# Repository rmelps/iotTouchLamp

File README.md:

<h1> Touch Lamp </h1>
<ul> 
<li> RGB LED lamp with color control through capacitive touch. </li>
<li> Wifi synchronization through each lamp in a system </li>
<li> ATMega168 Microcontroller project </li>
<li><i>Schematic coming soon</i></li>
</ul>

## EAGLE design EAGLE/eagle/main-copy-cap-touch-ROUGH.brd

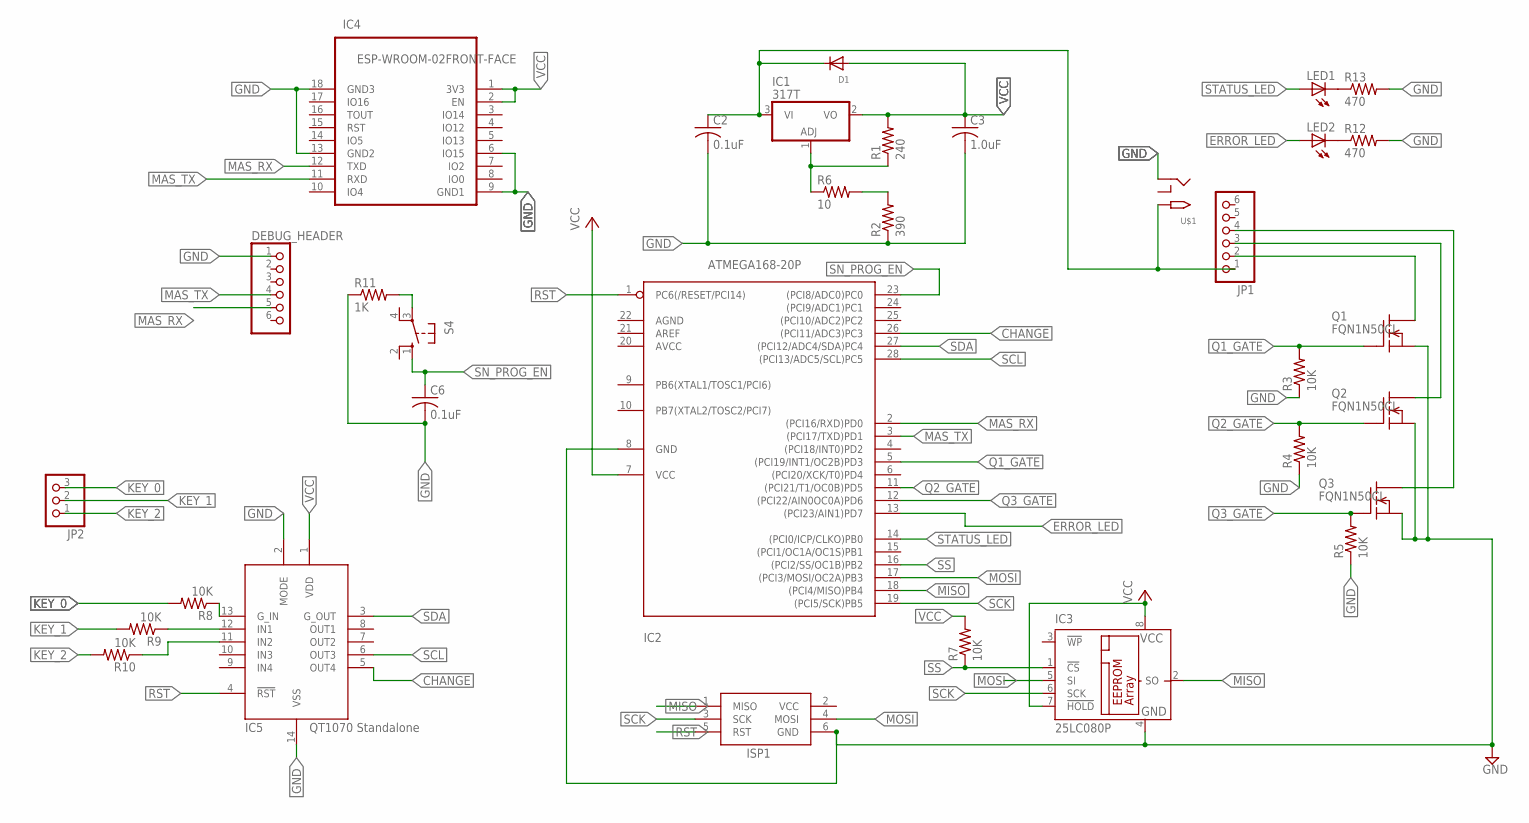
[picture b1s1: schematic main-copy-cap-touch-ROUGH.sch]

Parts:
C2, C6: 0.1uF; C025-030X050
C3: 1.0uF; C025-030X050
D1: DIODEDO-1N4148; DO-1N4148
DEBUG_HEADER: PINHD-1X6B; 1X06-BIG
IC1: 317T; TO220H
IC2: ATMEGA168-20P; DIL28-3
IC3: 25LC080P; DIL8
IC4: ESP-WROOM-02FRONT-FACE; FRONT-FACE
IC5: AT42QT1070-SSU; SO14
ISP1: AVRISP-6; AVRISP
JP1: PINHD-1X6B; 1X06-BIG
JP2: PINHD-1X3; 1X03
LED1, LED2: LED5MM
Q1, Q2, Q3: FQN1N50CI; TO92-INLINE
R1: 240; 0204/7
R2: 390; 0204/7
R3, R4, R5, R7, R8, R9, R10: 10K; 0204/7
R6: 10; 0204/7
R11: 1K; 0204/7
R12, R13: 470; 0204/7
S4: 10-XX; B3F-10XX
U$1: 2.1MMJACKTHM; PJ-102A

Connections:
CHANGE: IC2.26 ((PCI11/ADC3)PC3), IC5.5 (OUT4)
ERROR_LED: IC2.13 ((PCI23/AIN1)PD7), LED2.A
GND: C2.2, C3.2, C6.2, DEBUG_HEADER.1, IC2.8 (GND), IC3.4 (GND), IC4.6 (IO15), IC4.9 (GND1), IC4.13 (GND2), IC4.18 (GND3), IC5.2 (MODE), IC5.14 (VSS), ISP1.6 (GND), Q1.3 (S), Q2.3 (S), Q3.3 (S), R2.1, R3.1, R4.1, R5.1, R11.1, R12.2, R13.2, U$1.RING
KEY_0: JP2.3, R8.2
KEY_1: JP2.2, R9.2
KEY_2: JP2.1, R10.2
MAS_RX: DEBUG_HEADER.5, IC2.2 ((PCI16/RXD)PD0), IC4.12 (TXD)
MAS_TX: DEBUG_HEADER.4, IC2.3 ((PCI17/TXD)PD1), IC4.11 (RXD)
MISO: IC2.18 ((PCI4/MISO)PB4), IC3.2 (SO), ISP1.1 (MISO)
MOSI: IC2.17 ((PCI3/MOSI/OC2A)PB3), IC3.5 (SI), ISP1.4 (MOSI)
unnamed: IC5.13 (G_IN), R8.1
unnamed: IC5.12 (IN1), R9.1
unnamed: IC5.11 (IN2), R10.1
unnamed: R2.2, R6.2
unnamed: IC1.1 (ADJ), R1.1, R6.1
unnamed: JP1.2, Q1.1 (D)
unnamed: LED1.K (C), R13.1
unnamed: LED2.K (C), R12.1
unnamed: JP1.3, Q2.1 (D)
unnamed: JP1.4, Q3.1 (D)
unnamed: R11.2, S4.3
Q1_GATE: IC2.5 ((PCI19/INT1/OC2B)PD3), Q1.2 (G), R3.2
Q2_GATE: IC2.11 ((PCI21/T1/OC0B)PD5), Q2.2 (G), R4.2
Q3_GATE: IC2.12 ((PCI22/AIN0OC0A)PD6), Q3.2 (G), R5.2
RST: IC2.1 (PC6(/RESET/PCI14)), IC5.4 (!RST), ISP1.5 (RST)
SCK: IC2.19 ((PCI5/SCK)PB5), IC3.6 (SCK), ISP1.3 (SCK)
SCL: IC2.28 ((PCI13/ADC5/SCL)PC5), IC5.6 (OUT3)
SDA: IC2.27 ((PCI12/ADC4/SDA)PC4), IC5.3 (G_OUT)
SN_PROG_EN: C6.1, IC2.23 ((PCI8/ADC0)PC0), S4.1 (S)
SS: IC2.16 ((PCI2/SS/OC1B)PB2), IC3.1 (!CS), R7.1
STATUS_LED: IC2.14 ((PCI0/ICP/CLKO)PB0), LED1.A
VCC: C3.1, D1.A, IC1.2 (VO), IC2.7 (VCC), IC3.7 (!HOLD), IC3.8 (VCC), IC4.1 (3V3), IC4.2 (EN), IC5.1 (VDD), ISP1.2 (VCC), R1.2, R7.2
VIN: C2.1, D1.C, IC1.3 (VI), JP1.1, U$1.TIP

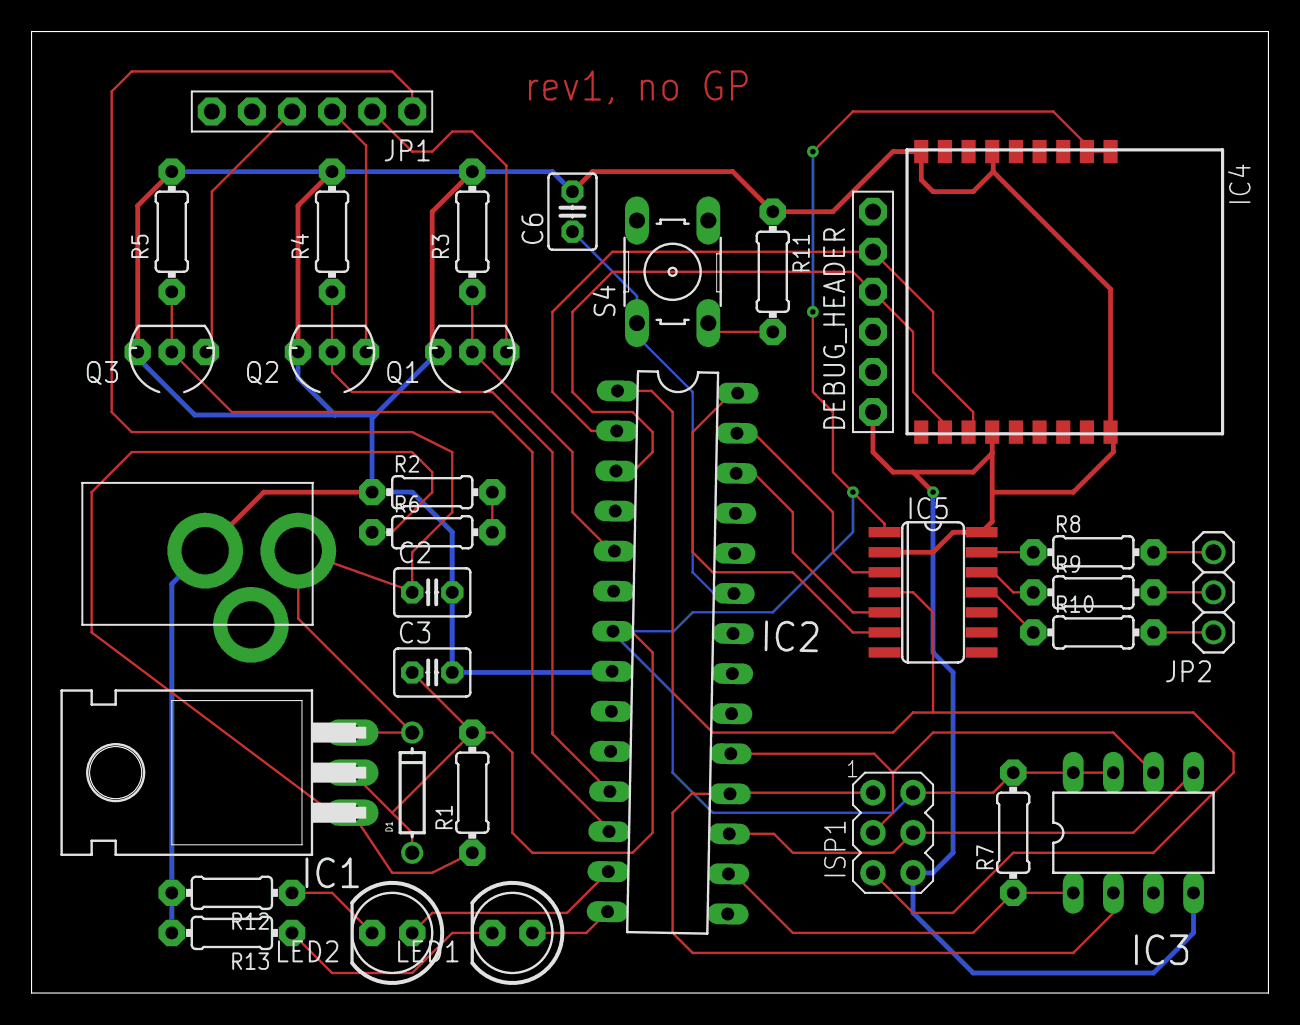
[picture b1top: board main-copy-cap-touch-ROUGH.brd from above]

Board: 2 copper layers, 78.4 x 61.0 mm, 33 parts (0 on the bottom side), 33 nets.

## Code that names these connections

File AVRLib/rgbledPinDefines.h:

// R Melpignano 18 DEC 2017
// ------------------------
// Pin defines for RGBLED Project with pushbutton inputs

// General pins controlling balance of RGB of LEDs

#define RLED 						PD5
#define GLED 						PD3
#define BLED						PD6

#define LED_PORT					PORTD
#define LED_PIN                 	PIND
#define LED_DDR                 	DDRD

#define RBUTTON						PC2
#define GBUTTON						PC1
#define BBUTTON						PC3

#define BUTTON_PORT					PORTC
#define BUTTON_PIN					PINC
#define BUTTON_DDR					DDRC

#define CHANGE_PORT					PORTC
#define CHANGE_PIN					PINC
#define CHANGE_DDR					DDRC
#define CHANGE_P					PC3

#define STATUS_LED					PB0
#define ERROR_LED					PC0

// Debug LEDs
#define DEBUG_0						PD2
#define DEBUG_1						PD4
#define DEBUG_2						PB6
#define DEBUG_3						PB7
#define DEBUG_01_DDR				DDRD
#define DEBUG_23_DDR				DDRB
#define DEBUG_01_PORT				PORTD
#define DEBUG_23_PORT				PORTB

#define DEBUG_0_ON					DEBUG_01_PORT |= (1 << DEBUG_0)
#define DEBUG_0_OFF					DEBUG_01_PORT &= ~(1 << DEBUG_0)
#define DEBUG_1_ON					DEBUG_01_PORT |= (1 << DEBUG_1)
#define DEBUG_1_OFF					DEBUG_01_PORT &= ~(1 << DEBUG_1)
#define DEBUG_2_ON					DEBUG_23_PORT |= (1 << DEBUG_2)
#define DEBUG_2_OFF					DEBUG_23_PORT &= ~(1 << DEBUG_2)
#define DEBUG_3_ON					DEBUG_23_PORT |= (1 << DEBUG_3)
#define DEBUG_3_OFF					DEBUG_23_PORT &= ~(1 << DEBUG_3)


// SPI port defines

#define SPI_SS                     	PB2
#define SPI_MOSI                    PB3
#define SPI_MISO                    PB4
#define SPI_SCK                     PB5

#define SPI_PORT               		PORTB
#define SPI_PIN                		PINB
#define SPI_DDR                		DDRB

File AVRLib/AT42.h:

// This file captures the I2C communication interface between the AT42 Capacitive Touch
// Sensor and the ATMega

// ----- Chip Address
#define AT42_READ					0x37
#define AT42_WRITE					0x36

// ----- Internal Register Addresses (Chapter 5 in Chip Manual)

// Current Status of all keys, indicating whether they are pressed or not (Read only)
#define DETECT_STATUS				0x02
#define KEY_STATUS					0x03

// Position of specific keys in key status byte
#define KEY_0						0
#define KEY_1						1
#define KEY_2						2
#define KEY_3						3
#define KEY_4						4
#define KEY_5						5
#define KEY_6						6

// Negative threshold (sensitivity) for keys (default = count 20, 0 == always detected) (R/W)
#define NEG_THRESH_0				0x20
#define NEG_THRESH_1				0x21
#define NEG_THRESH_2				0x22

// Averaging Factor/Adjacent Key Suppression, higher number = higher sample count = better SNR, but longer
// detection times (default = 0x01)
#define AKS_0						0x27
#define AKS_1						0x28
#define AKS_2						0x29

// Detection Integrator, number of consecutive measurements that must pass before flagging a key as
// "detected" (default = 4)
#define DI_0						0x2E
#define DI_1						0x2F
#define DI_2						0x30

// ----- Settings to initialize
#define NEG_THRESH_VAL				10
#define AKS_VAL						1
#define DI_VAL						4

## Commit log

2017-12-24 included libraries, working on SPI comms.
2017-12-25 trying again..
2017-12-26 nonvolatile memory added. Color data persists when the lights go out.
2018-01-05 organizing some AT commands into flash memory to be sent to ESP8266
2018-01-10 getting ready for actually configuring AT commands...right now just setting up the command queue as a struct list.
2018-01-16 starting to save ssid and pswd to eeprom for immediate fetch
2018-01-18 sequencing received messages from esp8266
2018-01-20 parsing query string, assigning to ssid and pass
2018-01-21 minor changes to query pparser function
2018-01-27 multiple routes for server requests
2018-01-28 accounting for /favicon route
2018-01-28 corrected AT_WAITING so that it doesnt fire before receiving a route
2018-01-30 got avr to talk to esp8266 and connect to wifi thru web browser hosted on esp8266
2018-02-01 adding firebase http functions for esp to make requests to
2018-02-03 able to poll and update database values, sort of messy right now, maybe someday ill clean it up
2018-02-07 can update lamp color from contents of GET request. Also added board schematics
2018-02-15 getting up to speed
2018-02-15 changed schematic
2018-02-17 starting I2C integration
2018-02-17 fixed one I2C.c thing I noticed
2018-02-18 none of this i2c stuff is tested, but mostly written into the code. thats probably not true either.
2018-02-18 noticed a copy and paste error
2018-02-19 finally testing this...seeing i2c errors causing it to not function at all...looking into this by adding DEBUG LEDs on PORTD and PORTB to track the flow
2018-02-19 still errors with i2c. made some progress. but still not close.
2018-02-23 trying inline TWI, without interrupts
2018-02-24 cleaning up
2018-02-28 got touch sense working over i2c
